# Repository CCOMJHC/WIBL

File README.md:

# Low-cost Data Logger System

## Purpose

This repository contains the hardware designs, firmware source code, and supporting applications and libraries for a low-cost data logger aimed at the NMEA ([National Marine Electronics Association](https://www.nmea.org)) 0183 and 2000 protocols, as used in many marine electronics systems.  The goal is to provide a minimally-functional system to record the data appearing on NMEA0183 and NMEA2000 busses on board ships, which can be used to provide volunteer depth observations (and many other things) to assist in mapping the oceans.

## Why Have Another Logger?

There is a robust infrastructure of data loggers for both NMEA0183 and NMEA2000 busses, but they are often intended for different purposes (e.g., voyage data recorders, WiFi gateways, etc.), and they are typically order US$250 [2020] or more.  This project came out of efforts within the [Seabed 2030](https://seabed2030.gebco.net) project to map the world ocean completely by 2030, where large-scale mapping is required if the goals of the programme are to be met.  Consequently, while volunteer data is a part of the solution, it has to be something that can be scaled to very large data collections.  Since it has proven hard to sustain open data collection of this type (most of the sustained efforts have been closed, with data only going back to the collectors, and not to open databases), we believe that the only viable financial model for this purpose is to give the hardware away for free, rather than attempting to sell it for profit.  That is, the hardware is free to the data collector, who is asked just to host the hardware on their ship.  Because of this model, we need the hardware to be as low-cost as possible.

This project is therefore aimed at designing as simple, and low-cost, a logger as possible, so that as many as possible can be built and distributed to assist in mapping the oceans.  The target price is order US$30 [2020] for one interface (either NMEA0183 or NMEA2000), or US$40 [2020] for both interfaces.

At the same time, we recognise that getting data from the loggers into the national and international databases can be difficult, and ask a lot of the volunteer data collectors.  The project is therefore also attempting to define a workflow for submission of data to the [International Hydrographic Office](https://iho.int)'s [Data Center for Digital Bathymetry](https://www.ngdc.noaa.gov/iho/), hosted by the [National Centers for Environmental Information](https://www.ngdc.noaa.gov) in Boulder, CO.  The goal is to have a "Trusted Node in a Box", so that anyone wanting to support collection of data of this kind has everything they need to support a very basic data flowpath direct from the loggers through the cloud to DCDB.  (Developers are then free to add on anything else they need.)

## What Does the Logger Do?

The logger's functionality is deliberately constrained.  During normal operations, the logger monitors the NMEA0183 and/or NMEA2000 busses to which it is attached, and records any valid data packet received to local storage.  Timestamps are provided through the elapsed time counter on the microcontroller used, and although a pseudo-time is computed from NMEA2000 data packets if they are available, there is no expectation that timestamps will be assigned until the data is uploaded for processing.

The logger provides a WiFi interface for monitoring, configuration, and control.  If there's no other option, the logger will provide its own access point (i.e., create its own WiFi network) to which users can connect, but it can also be configured to connect to a mobile hotspot or an infrastructure WiFi network if available.  The logger runs a web server so that any modern browser can be used to interact with the system (the logger provides the HTML and JavaScript for all required functionality), and also provides an API to send simple commands using a custom language and receive JSON-format responses for a programmatic interface.

After upload to a mobile collection device (e.g., a cell-phone or tablet), or direct uploading (via a separate upload server, also included, if the logger is on an infrastructure network with internet connection), the data is sent to Amazon Web Services, at which point it is processed, reformatted, packaged, and transmitted to DCDB for archive.

## Concept of Operations

This logger is designed for supported, focussed, data collections.  In this mode, loggers would be provided by an organisation in a specific geographic location to support data collection in a particular area.  The goal here is to provide density of observations in an area, which greatly assists in processing the data, and making useful products.  In addition to providing the loggers (and recruiting the volunteer observers), the organisation would also provide local support personnel to visit the volunteer observers, pick up the collected data (via mobile device or through maintaining an upload server), and make sure that the loggers were still collecting data.  Having local support also ensures that there is continued communication with the observers, which is useful in sustaining the community in the long term.

After each visit, all of the data collected (potentially from multiple observers) on the mobile device can be uploaded to any available service that implements the cloud segment of the software suite.  This could be something set up specifically for the organisation using the model provided here, or it could be a third-party that provides an equivalent.

## Licensing and Distribution

In order to provide for the widest possible use (and to avoid excuses ...) the hardware designs, firmware source, and supporting libraries are all released as Open Source under the MIT license.  The cloud segment is released under the MIT License for non-commercial use; for commercial licenses, please contact info@ccom.unh.edu.

## Where to Start

See the "Logger firmware" section below to get started with the WIBL loggers. 
See the "Data management" section below to get started using WIBL and 
`wibl-python` tools to manage and process data generated by WIBL loggers.

### Logger firmware

The source for the system is maintained in a [GitHub repository](https://github.com/CCOMJHC/WIBL), which also includes a [Wiki](https://github.com/CCOMJHC/WIBL/wiki) for details of the design and system development.  The Wiki is the most useful source of current information to set up and programme the logger firmware, and to access the rest of the code resources.

To build the firmware and work with the hardware designs, you will need at least:

1. A functional Python interpreter (at least 3.13) (e.g., [MiniConda](https://www.anaconda.com/docs/getting-started/miniconda/main)).

2. A working copy of [VSCode](https://code.visualstudio.com) and [PlatformIO](https://platformio.org) to build the firmware and other logger functionality.

3. Support for NMEA2000 handling on ESP32 (you need the [base library](https://github.com/ttlappalainen/NMEA2000) and [ESP-specific](https://github.com/ttlappalainen/NMEA2000_esp32) extensions).

4. [KiCAD](https://www.kicad.org) (at least 9.0) to examine and edit the logger schematic and board layout.

5. [FreeCAD](https://www.freecad.org) (at least 1.0) to examine and edit the logger enclosure STEP files.

6. A working C++11 (at least) compiler for the software data simulator (the installation with VSCode works very well).

With these prerequisites, the recommended place to start is with the logger firmware, followed by the post-processing Python code, which will allow you to demonstrate that your logger is actually logging data.  For benchtop testing, the hardware data simulator can be used to generate simulated data on both NMEA0183 and NMEA2000 buses for testing logger modifications.

### Data management

The included [wibl-python](wibl-python/README.md) tools allow data from WIBL 
loggers to be processed into GeoJSON format and to be submitted to 
[DCDB](https://www.ngdc.noaa.gov/iho/). There is also a tool called 
[LogConvert](LogConvert) that allows data from TeamSurv and Yacht Devices
loggers to be converted to WIBL format for further processing using 
`wibl-python`.

An easy way to use both `wibl-python` and `LogConvert` is to use the official
WIBL [container images](DataManagement/containers/README.md).

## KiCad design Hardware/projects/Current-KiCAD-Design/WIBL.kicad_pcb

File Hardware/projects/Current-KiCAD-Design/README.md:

# KiCAD Hardware Design Files

## Introduction

This directory contains all of the files required for the [KiCAD](https://www.kicad.org) projects associated with the [WIBL](https://wibl.ccom.unh.edu) project.  You will need at least v. 10.0 of KiCAD to use the files.

## Portability

There have been some reported issues with project files containing hard-coded directory and filenames, which makes them a little less portable than would be preferred.  If this happens, you can point at the new location of schematic symbols and footprint libraries by:

1. Open [the project file](WIBL.kicad_pro) in KiCAD.
2. Open menu Peferences > Manage Symbol Libraries
    - Switch to the "Project Specific Libraries" tab.
    - Click on the cell containing the pathname for the "WIBL-sym" library, and navigate to the [WIBL.kicad_sym](WIBL.kicad_sym) file.
    - Click "OK" to save.
3. Open menu Preferences > Manage Footprint Libraries
    - Switch to the "Project Specific Libraries" tab.
    - Click on the cell containing the pathname for the "WIBL" library, and navigate to the [WIBL.pretty](WIBL.pretty/) directory.
    - Click "OK" to save.

After this, you can check that the project is working appropriately by using the Electrical Rules Check (ERC) in schematic editor, and Design Rules Check (DRC) in PCB editor.  There may be one or two warnings, but there shouldn't be a tonne of warnings about missing libraries or symbols.

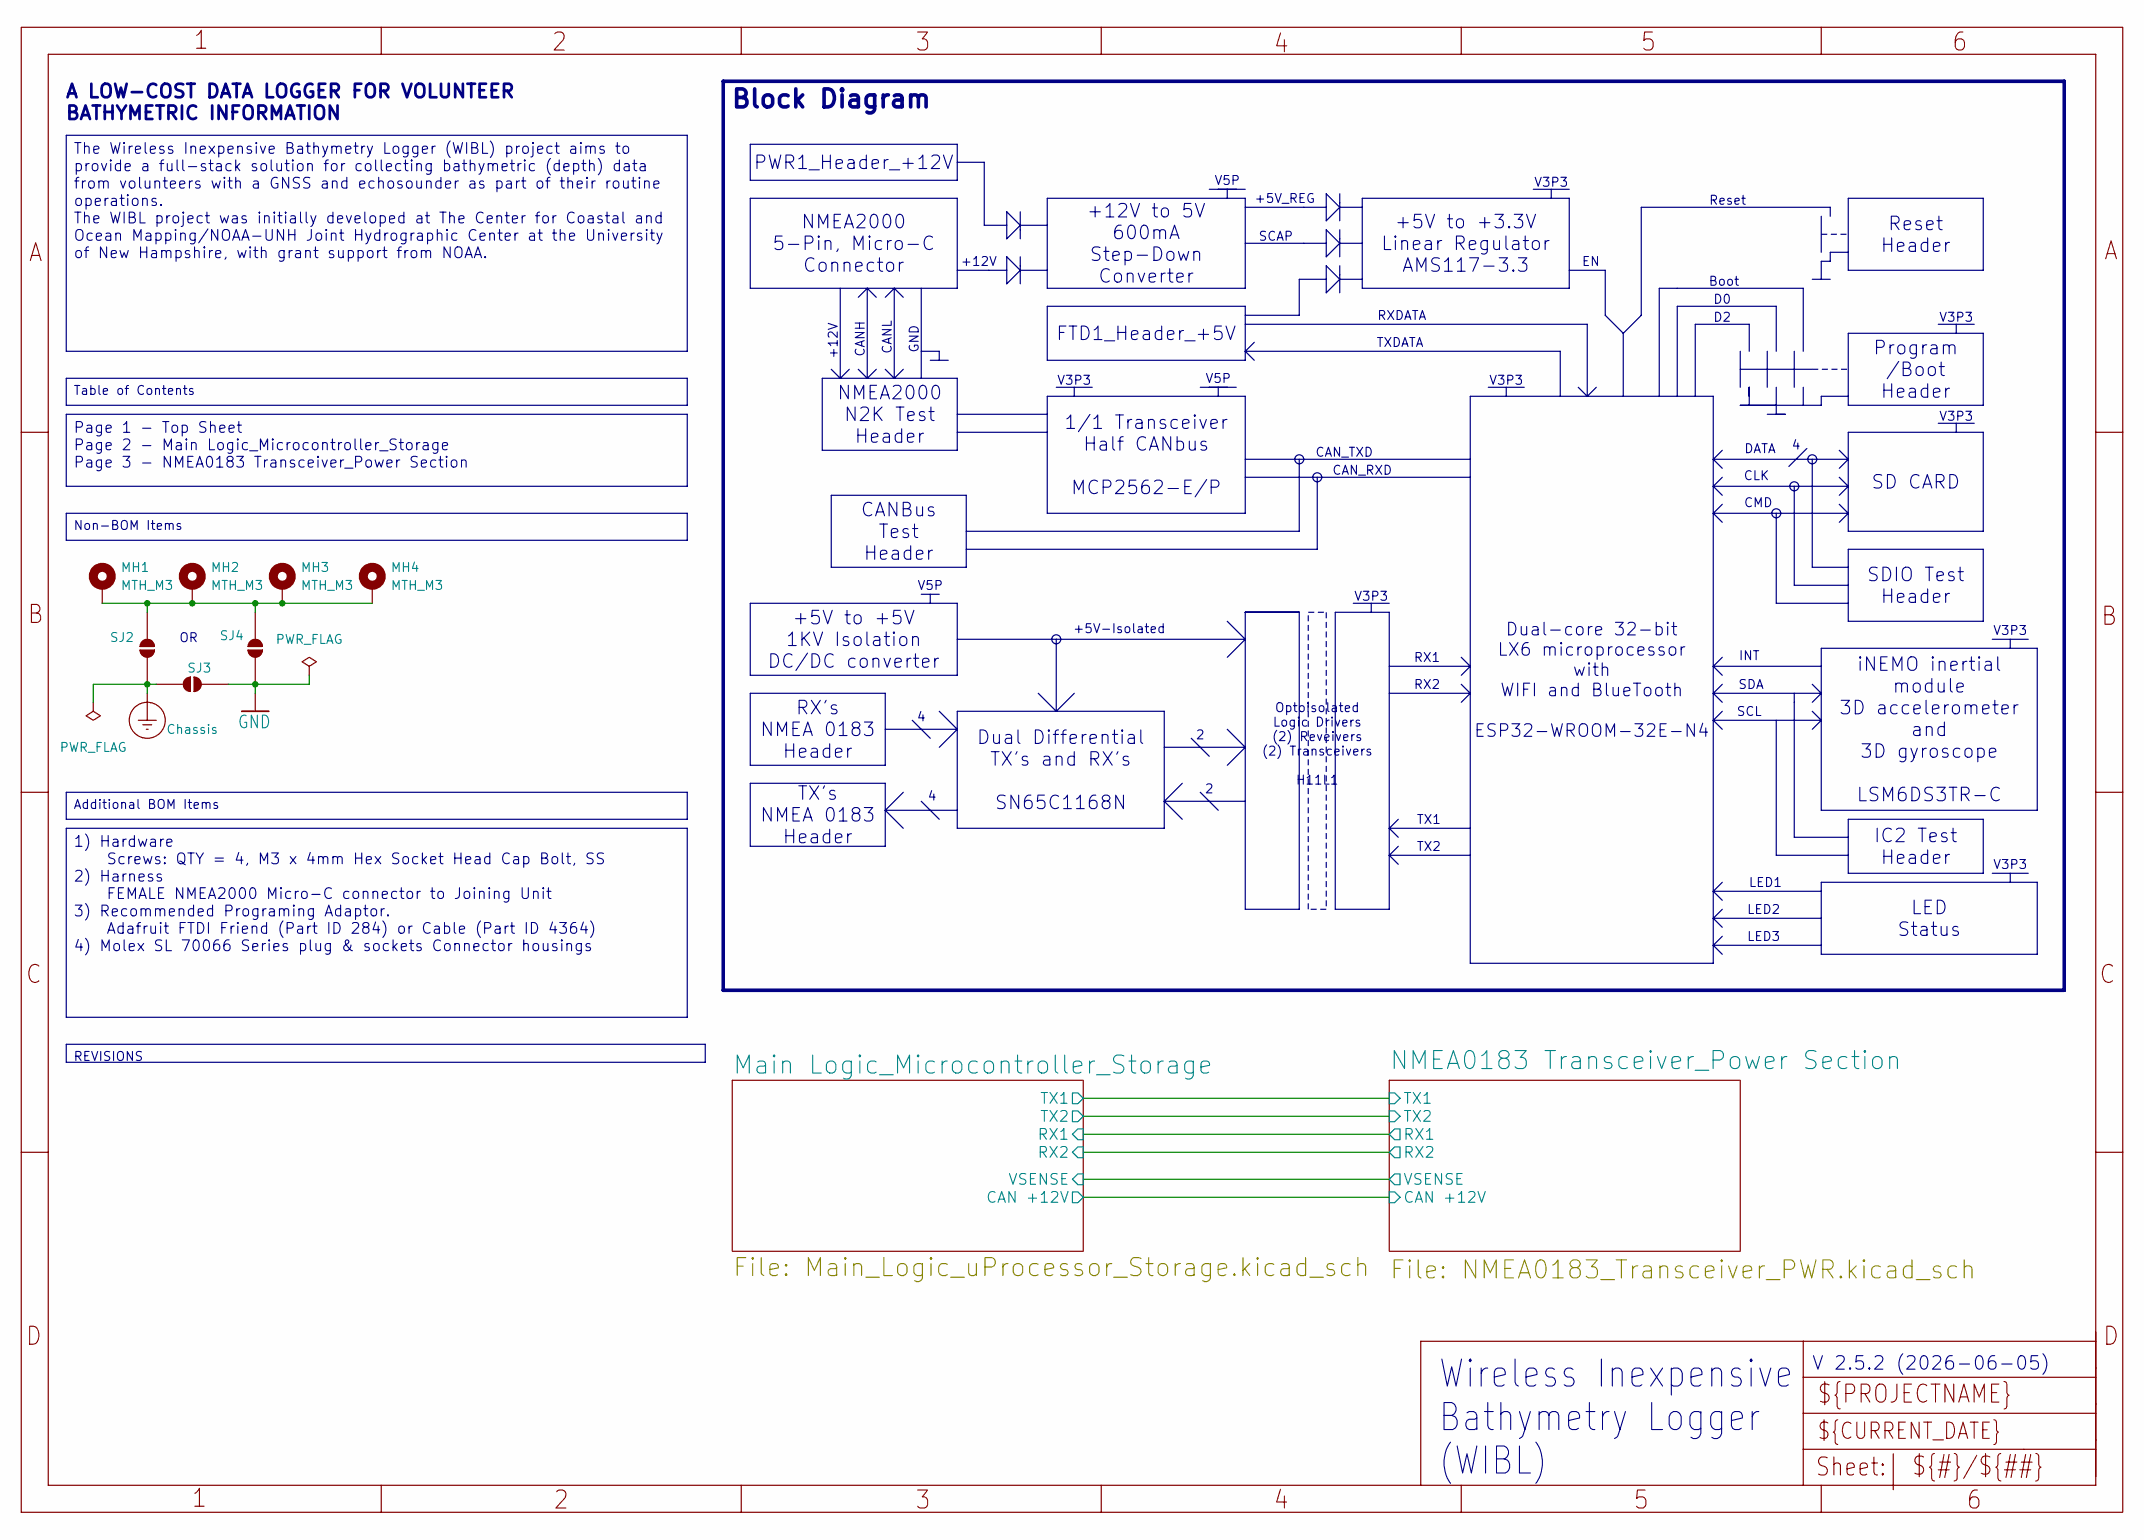
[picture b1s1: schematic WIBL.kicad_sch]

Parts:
MH1, MH2, MH3, MH4: MTH_M3; MountingHole_3.2mm_M3_DIN965_Pad_TopBottom
SJ2, SJ3, SJ4: SJ_NO; SolderJumper-2_P1.3mm_Open_RoundedPad1.0x1.5mm

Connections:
Chassis: SJ2.1 (A), SJ3.2 (B); also elsewhere on the board
GND: SJ3.1 (A), SJ4.1 (A); also elsewhere on the board
unnamed: MH1.1 (1_1), MH2.1 (1_1), MH3.1 (1_1), MH4.1 (1_1), SJ2.2 (B), SJ4.2 (B)

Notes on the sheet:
+5V_REG
V5P
V3P3
RX1
V 2.5.2 (2026-06-05)
TX1
CMD
+5V-Isolated
LED3
CANL
RX2
DATA
CAN_RXD
SCL
Reset
Boot
CANH
GND
SDA
TXDATA
A LOW-COST DATA LOGGER FOR VOLUNTEER BATHYMETRIC INFORMATION
+12V
RXDATA
Wireless Inexpensive Bathymetry Logger (WIBL)
TX2
Optoisolated Logic Drivers (2) Reveivers (2) Transceivers H11L1
LED1
LED2
CAN_TXD
SCAP
CLK
INT
TX's NMEA 0183 Header
REVISIONS
1) Hardware Screws: QTY = 4, M3 x 4mm Hex Socket Head Cap Bolt, SS 2) Harness FEMALE NMEA2000 Micro-C connector to Joining Unit 3) Recommended Programing Adaptor. Adafruit FTDI Friend (Part ID 284) or Cable (Part ID 4364) 4) Molex SL 70066 Series plug & sockets Connector housings
SDIO Test Header
Page 1 - Top Sheet Page 2 - Main Logic_Microcontroller_Storage Page 3 - NMEA0183 Transceiver_Power Section
FTD1_Header_+5V
Dual Differential TX's and RX's SN65C1168N
+12V to 5V 600mA Step-Down Converter

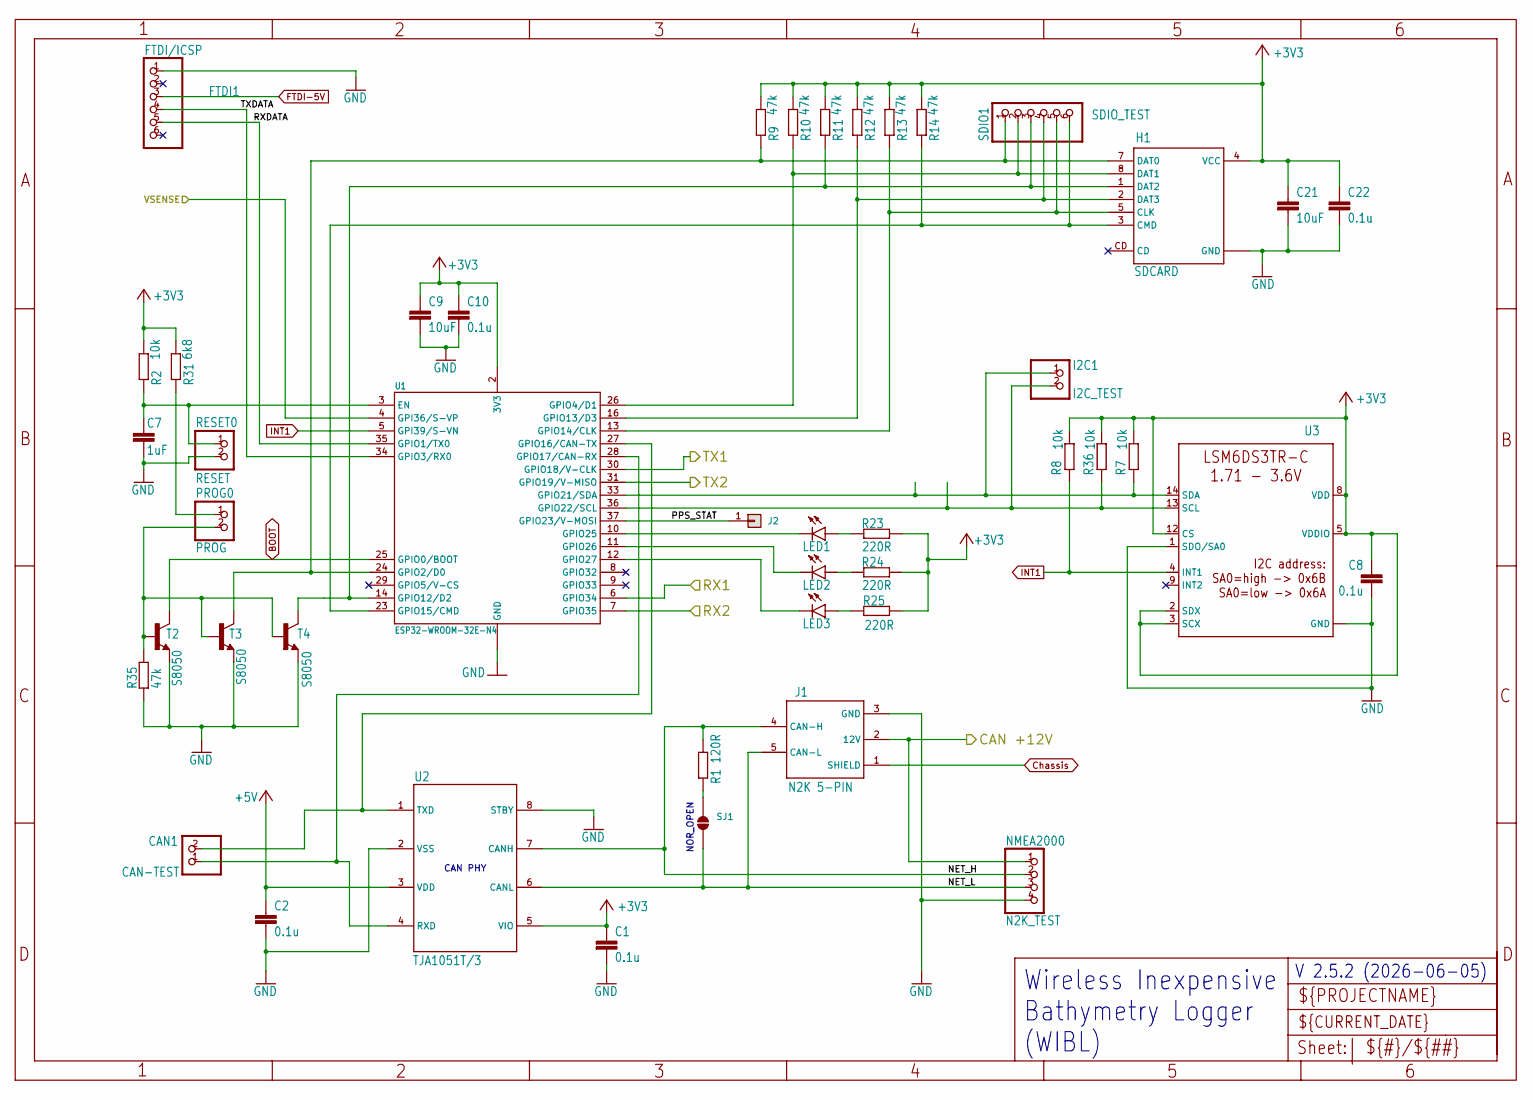
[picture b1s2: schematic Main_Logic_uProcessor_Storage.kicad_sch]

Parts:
C1, C2, C8, C10, C22: 0.1u; C0805_334
C7: 1uF; C0805_334
C9, C21: 10uF; C0805_334
CAN1: CAN-TEST; 1X02_325_254mm; MPNum PZ254V-11-02P
FTDI1: FTDI/ICSP; 1X06_325_254mm; MPNum PZ254V-11-06P
H1: SDCARD; XUNPU-MICROSD-SOCKET; MPNum TF-115
I2C1: I2C_TEST; 1X02_325_254mm; MPNum PZ254V-11-02P
J1: N2K 5-PIN; NMEA2000; MPNum HMC-05PMMS-SF8001
J2: Conn_01x01; PinHeader_1x01_P2.54mm_Vertical
LED1: LEDCHIP-LED0603; CHIP-LED0603_259; MPNum 19-213/Y2C-CQ2R2L/3T(CY)
LED2: LEDCHIP-LED0603; CHIP-LED0603_259; MPNum 19-217/GHC-YR1S2/3T
LED3: LEDCHIP-LED0603; CHIP-LED0603_259; MPNum 19-217/BHC-ZL1M2RY/3T
NMEA2000: N2K_TEST; 1X04_325_254mm; MPNum PZ254V-11-04P
PROG0: PROG; 1X02_325_254mm; MPNum PZ254V-11-02P
R1: 120R; R0805_334
R2, R7, R8, R36: 10k; R0805_334
R9, R10, R11, R12, R13, R14, R35: 47k; R0805_334
R23, R24, R25: 220R; R0805_334
R31: 6k8; R0805_334
RESET0: RESET; 1X02_325_254mm; MPNum PZ254V-11-02P
SDIO1: SDIO_TEST; 1X06_325_254mm; MPNum PZ254V-11-06P
SJ1: SJ_NO; SolderJumper-2_P1.3mm_Open_RoundedPad1.0x1.5mm
T2, T3, T4: S8050; SOT23_402; MPNum S8050
U1: ESP32-WROOM-32E-N4; ESPS32-WROOM-32E; MPNum ESP32-WROOM-32E-N4
U2: TJA1051T/3; SOIC8; MPNum MCP2562T-E/SN
U3: LSM6DS3TR-C; LGA-14-2.5X3MM; MPNum LSM6DS3TR-C

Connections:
+3V3: C1.1, C8.1, C9.1, C10.1, C21.1, C22.1, H1.4 (VCC), R2.2, R7.2, R8.2, R9.2, R10.2, R11.2, R12.2, R13.2, R14.2, R23.1, R24.1, R25.1, R31.2, R36.2, U1.2 (3V3), U2.5 (VIO), U3.2 (SDX), U3.3 (SCX), U3.5 (VDDIO), U3.8 (VDD), U3.12 (CS); also elsewhere on the board
+5V: C2.1, U2.3 (VDD); also elsewhere on the board
/Main Logic_Microcontroller_Storage/CAN +12V: J1.2 (12V), NMEA2000.1; also elsewhere on the board
/Main Logic_Microcontroller_Storage/NET_H: J1.4 (CAN-H), NMEA2000.2, R1.2, U2.7 (CANH)
/Main Logic_Microcontroller_Storage/NET_L: J1.5 (CAN-L), NMEA2000.3, SJ1.1 (A), U2.6 (CANL)
/Main Logic_Microcontroller_Storage/PPS_STAT: J2.1 (Pin_1_1), U1.37 (GPIO23/V-MOSI)
/Main Logic_Microcontroller_Storage/RX1: U1.6 (GPIO34); also elsewhere on the board
/Main Logic_Microcontroller_Storage/RX2: U1.7 (GPIO35); also elsewhere on the board
/Main Logic_Microcontroller_Storage/RXDATA: FTDI1.5, U1.35 (GPIO1/TX0)
/Main Logic_Microcontroller_Storage/TX1: U1.30 (GPIO18/V-CLK); also elsewhere on the board
/Main Logic_Microcontroller_Storage/TX2: U1.31 (GPIO19/V-MISO); also elsewhere on the board
/Main Logic_Microcontroller_Storage/TXDATA: FTDI1.4, U1.34 (GPIO3/RX0)
/NMEA0183 Transceiver_Power Section/VSENSE: U1.4 (GPI36/S-VP); also elsewhere on the board
BOOT: T2.3 (C), U1.25 (GPIO0/BOOT); also elsewhere on the board
Chassis: J1.1 (SHIELD); also elsewhere on the board
FTDI-5V: FTDI1.3; also elsewhere on the board
GND: C1.2, C2.2, C7.2, C8.2, C9.2, C10.2, C21.2, C22.2, FTDI1.1, H1.6 (GND), H1.GND1 (GND), H1.GND2 (GND), H1.GND3 (GND), H1.GND4 (GND), J1.3 (GND), NMEA2000.4, R35.1, RESET0.2, T2.2 (E), T3.2 (E), T4.2 (E), U1.1 (GND), U1.15 (GND), U1.38 (GND), U1.THERM (GND), U2.2 (VSS), U2.8 (STBY), U3.1 (SDO/SA0), U3.6 (GND), U3.7 (GND); also elsewhere on the board
INT1: R8.1, U1.5 (GPI39/S-VN), U3.4 (INT1)
unnamed: H1.5 (CLK), R13.1, SDIO1.5, U1.13 (GPIO14/CLK)
unnamed: H1.3 (CMD), R14.1, SDIO1.6, U1.23 (GPIO15/CMD)
unnamed: H1.7 (DAT0), R9.1, SDIO1.1, T3.3 (C), U1.24 (GPIO2/D0)
unnamed: H1.8 (DAT1), R10.1, SDIO1.2, U1.26 (GPIO4/D1)
unnamed: H1.1 (DAT2), R11.1, SDIO1.3, T4.3 (C), U1.14 (GPIO12/D2)
unnamed: H1.2 (DAT3), R12.1, SDIO1.4, U1.16 (GPIO13/D3)
unnamed: LED1.A, R23.2
unnamed: LED2.A, R24.2
unnamed: LED3.A, R25.2
unnamed: PROG0.1, R31.1
unnamed: R1.1, SJ1.2 (B)
unnamed: PROG0.2, R35.2, T2.1 (B), T3.1 (B), T4.1 (B)
unnamed: C7.1, R2.1, RESET0.1, U1.3 (EN)
unnamed: CAN1.2, U1.27 (GPIO16/CAN-TX), U2.1 (TXD)
unnamed: CAN1.1, U1.28 (GPIO17/CAN-RX), U2.4 (RXD)
unnamed: I2C1.1, R7.1, U1.33 (GPIO21/SDA), U3.14 (SDA)
unnamed: I2C1.2, R36.1, U1.36 (GPIO22/SCL), U3.13 (SCL)
unnamed: LED1.C, U1.10 (GPIO25)
unnamed: LED2.C, U1.11 (GPIO26)
unnamed: LED3.C, U1.12 (GPIO27)

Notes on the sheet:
Wireless Inexpensive Bathymetry Logger (WIBL)
V 2.5.2 (2026-06-05)
CAN PHY
NOR_OPEN

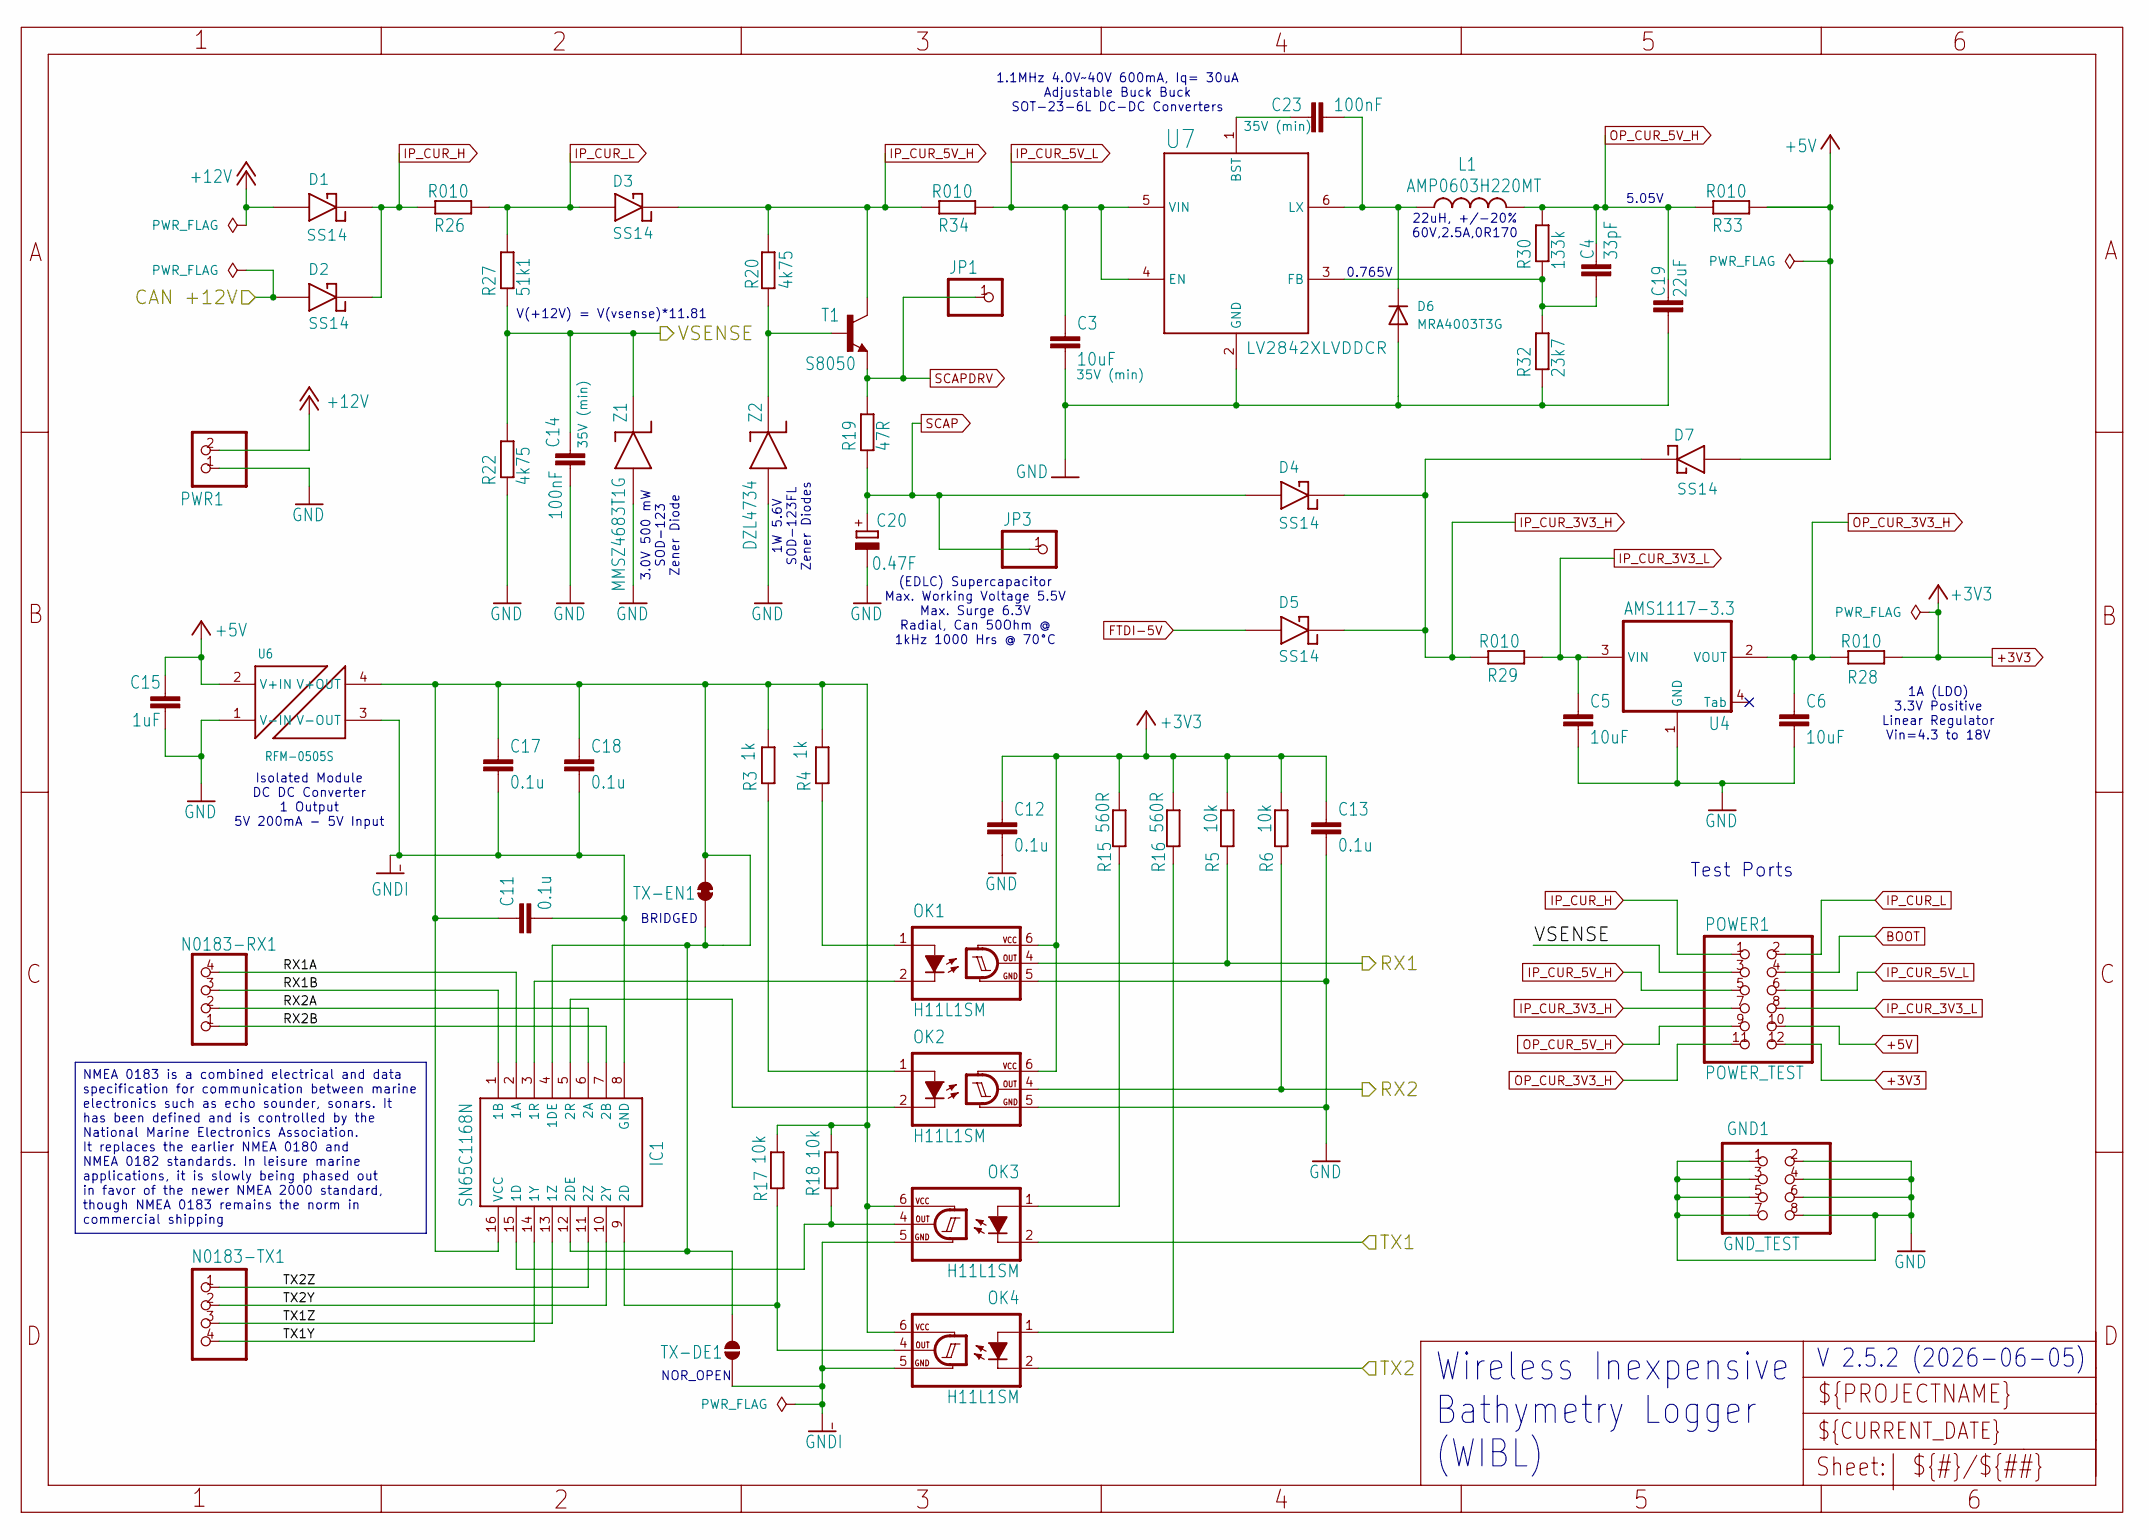
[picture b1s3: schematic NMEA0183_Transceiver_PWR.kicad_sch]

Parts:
C3: 10uF; C1206_334; Voltage 35V (min)
C4: 33pF; C0603_334
C5, C6: 10uF; C0805_334
C11, C12, C13, C17, C18: 0.1u; C0805_334
C14: 100nF; C0402; Voltage 35V (min)
C15: 1uF; C0805_334
C19: 22uF; C0603_334
C20: 0.47F; P128-50_334; Working Voltage 5.5V; MPNum KR-5R5C474-R
C23: 100nF; C0402
D1, D2, D3, D4, D5, D7: SS14; DO-214AC; MPNum SS14
D6: MRA4003T3G; DO-214AC_p12
GND1: GND_TEST; 2X04_325; MPNum PZ254V-12-4P
IC1: SN65C1168N; DIP794W53P254L1930H508Q16N; MPNum SN65C1168N
JP1, JP3: PINHD-1X1; 1X01_325_254mm; MPNum PZ254V-11-01P
L1: AMP0603H220MT; MWSA0603S; MPNum AMP0603H220MT, MWSA0603S-220MT
N0183-RX1: PINHD-1X4; 1X04_325_254mm; MPNum PZ254V-11-04P
N0183-TX1: TX_TEST; 1X04_325_254mm; MPNum PZ254V-11-04P
OK1, OK2, OK3, OK4: H11L1SM; DIL6-SMD_320; MPNum H11L1SM
POWER1: POWER_TEST; 2X06_325; MPNum PZ254V-12-6P
PWR1: PINHD-1X2; 1X02_325_254mm; MPNum PZ254V-11-02P
R3, R4: 1k; R0805_334
R5, R6, R17, R18: 10k; R0805_334
R15, R16: 560R; R0805_334
R19: 47R; R0805_334
R20: 4k75; R0805_334
R22: 4k75; R0603_334
R26, R28, R29, R33, R34: R010; R0603_334
R27: 51k1; R0603_334
R30: 133k; R0603_334
R32: 23k7; R0603_334
T1: S8050; SOT23_402; MPNum S8050
TX-DE1: SJ_NO; SolderJumper-2_P1.3mm_Open_RoundedPad1.0x1.5mm
TX-EN1: SJ_NC; SolderJumper-2_P1.3mm_Bridged2Bar_Pad1.0x1.5mm
U4: AMS1117-3.3; SOT223_111; Voltage (V) 3.3; MPNum UMW AMS1117-3.3
U6: RFM-0505S; MPNum RFM-0505S
U7: LV2842XLVDDCR; SOT-23-6L; MPNum LV2842XLVDDCR
Z1: MMSZ4683T1G; SOD123; Voltage 3V; MPNum BZT52C3V0-7-F
Z2: DZL4734; SOD-123FL; MPNum DZL4734

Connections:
+3V3: C12.1, C13.1, OK1.6 (VCC), OK2.6 (VCC), POWER1.12, R5.2, R6.2, R15.2, R16.2, R28.1; also elsewhere on the board
+5V: C15.1, D7.A, POWER1.10, R33.1, U6.2 (V+IN); also elsewhere on the board
+12V: D1.A, PWR1.2
/Main Logic_Microcontroller_Storage/CAN +12V: D2.A; also elsewhere on the board
/Main Logic_Microcontroller_Storage/RX1: OK1.4 (OUT), R5.1; also elsewhere on the board
/Main Logic_Microcontroller_Storage/RX2: OK2.4 (OUT), R6.1; also elsewhere on the board
/Main Logic_Microcontroller_Storage/TX1: OK3.2 (C); also elsewhere on the board
/Main Logic_Microcontroller_Storage/TX2: OK4.2 (C); also elsewhere on the board
/NMEA0183 Transceiver_Power Section/RX1A: IC1.2 (1A), N0183-RX1.4
/NMEA0183 Transceiver_Power Section/RX1B: IC1.1 (1B), N0183-RX1.3
/NMEA0183 Transceiver_Power Section/RX2A: IC1.6 (2A), N0183-RX1.2
/NMEA0183 Transceiver_Power Section/RX2B: IC1.7 (2B), N0183-RX1.1
/NMEA0183 Transceiver_Power Section/TX1Y: IC1.14 (1Y), N0183-TX1.4
/NMEA0183 Transceiver_Power Section/TX1Z: IC1.13 (1Z), N0183-TX1.3
/NMEA0183 Transceiver_Power Section/TX2Y: IC1.10 (2Y), N0183-TX1.2
/NMEA0183 Transceiver_Power Section/TX2Z: IC1.11 (2Z), N0183-TX1.1
/NMEA0183 Transceiver_Power Section/VSENSE: C14.P$1 (1), POWER1.3, R22.2, R27.1, Z1.2 (K); also elsewhere on the board
BOOT: POWER1.4; also elsewhere on the board
FTDI-5V: D5.A; also elsewhere on the board
GND: C3.2, C5.2, C6.2, C12.2, C13.2, C14.P$2 (2), C15.2, C19.1, C20.-, D6.2 (A), GND1.1, GND1.2, GND1.3, GND1.4, GND1.5, GND1.6, GND1.7, GND1.8, OK1.5 (GND), OK2.5 (GND), PWR1.1, R22.1, R32.1, U4.1 (GND), U6.1 (V-IN), U7.2 (GND), Z1.1 (A), Z2.A; also elsewhere on the board
GNDI: C11.2, C17.2, C18.2, IC1.8 (GND), OK3.5 (GND), OK4.5 (GND), TX-DE1.1 (A), U6.3 (V-OUT)
IP_CUR_3V3_H: D4.K, D5.K, D7.K, POWER1.7, R29.2
IP_CUR_3V3_L: C5.1, POWER1.8, R29.1, U4.3 (VIN)
IP_CUR_5V_H: D3.K, POWER1.5, R20.2, R34.2, T1.3 (C)
IP_CUR_5V_L: C3.1, POWER1.6, R34.1, U7.4 (EN), U7.5 (VIN)
IP_CUR_H: D1.K, D2.K, POWER1.1, R26.2
IP_CUR_L: D3.A, POWER1.2, R26.1, R27.2
unnamed: C23.P$1 (1), U7.1 (BST)
unnamed: C23.P$2 (2), D6.1 (K), L1.P$1 (1), U7.6 (LX)
unnamed: IC1.15 (1D), OK3.4 (OUT), R18.1
unnamed: C11.1, C17.1, C18.1, IC1.4 (1DE), IC1.12 (2DE), IC1.16 (VCC), OK3.6 (VCC), OK4.6 (VCC), R3.2, R4.2, R17.2, R18.2, TX-DE1.2 (B), TX-EN1.1 (A), TX-EN1.2 (B), U6.4 (V+OUT)
unnamed: IC1.3 (1R), OK1.2 (C)
unnamed: IC1.9 (2D), OK4.4 (OUT), R17.1
unnamed: IC1.5 (2R), OK2.2 (C)
unnamed: OK1.1 (A), R4.1
unnamed: OK2.1 (A), R3.1
unnamed: OK3.1 (A), R15.1
unnamed: OK4.1 (A), R16.1
unnamed: R20.1, T1.1 (B), Z2.K
unnamed: C4.1, R30.1, R32.2, U7.3 (FB)
OP_CUR_3V3_H: C6.1, POWER1.11, R28.2, U4.2 (VOUT)
OP_CUR_5V_H: C4.2, C19.2, L1.P$2 (2), POWER1.9, R30.2, R33.2
SCAP: C20.+, D4.A, JP3.1 (1_1), R19.1
SCAPDRV: JP1.1 (1_1), R19.2, T1.2 (E)

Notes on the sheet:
0.765V
5.05V
1A (LDO) 3.3V Positive Linear Regulator Vin=4.3 to 18V
1W 5.6V SOD-123FL Zener Diodes
3.0V 500 mW SOD-123 Zener Diode
V(+12V) = V(vsense)*11.81
Test Ports
Isolated Module DC DC Converter 1 Output 5V 200mA - 5V Input
1.1MHz 4.0V~40V 600mA, Iq= 30uA Adjustable Buck Buck SOT-23-6L DC-DC Converters
22uH, +/-20% 60V,2.5A,0R170
V 2.5.2 (2026-06-05)
NOR_OPEN
BRIDGED
(EDLC) Supercapacitor Max. Working Voltage 5.5V Max. Surge 6.3V Radial, Can 50Ohm @ 1kHz 1000 Hrs @ 70°C
Wireless Inexpensive Bathymetry Logger (WIBL)
NMEA 0183 is a combined electrical and data specification for communication between marine electronics such as echo sounder, sonars. It has been defined and is controlled by the National Marine Electronics Association. It replaces the earlier NMEA 0180 and NMEA 0182 standards. In leisure marine app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

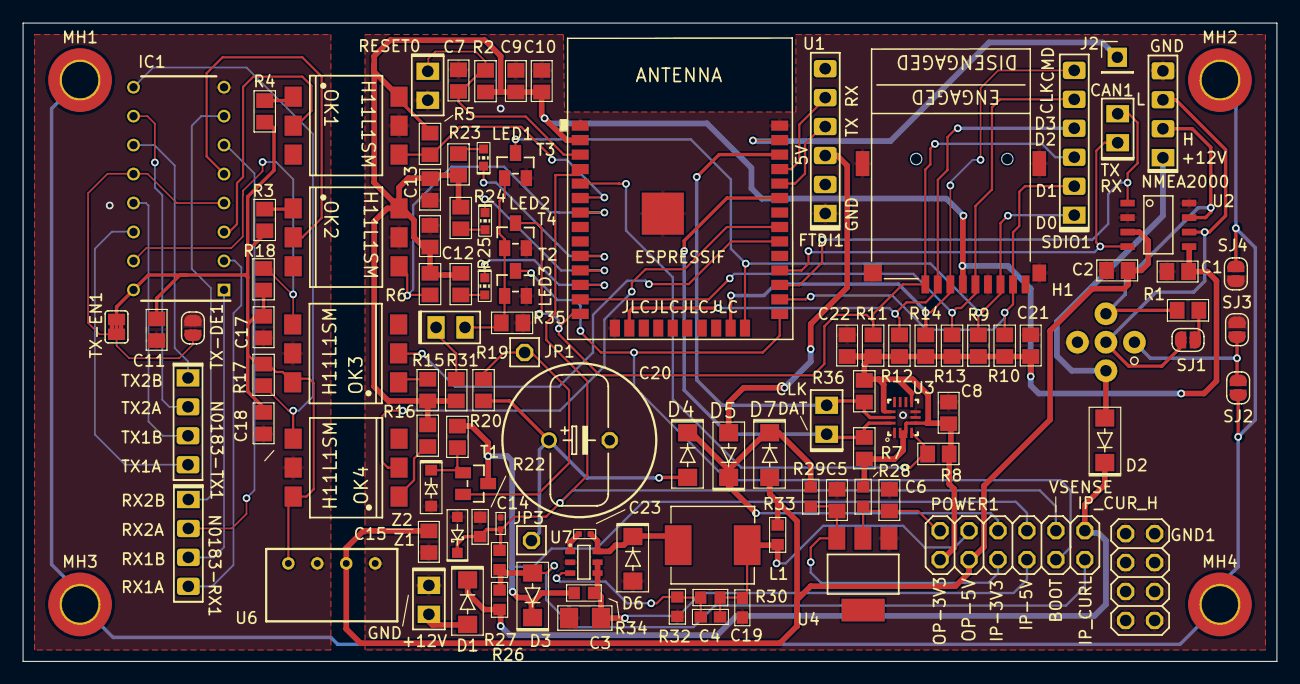
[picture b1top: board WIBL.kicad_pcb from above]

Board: 2 copper layers, 110.0 x 56.0 mm, 113 parts (1 on the bottom side), 72 nets.

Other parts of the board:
G1: LOGO; CCOM_JHC_Logo_rt_18mm

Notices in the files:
Hardware/projects/Current-KiCAD-Design/WIBL.kicad_pcb:
(c) 2025 Center for Coastal and Ocean Mapping
Hardware/projects/TCB-GNSS-Board/WIBL-TCB.kicad_pcb:
https://creativecommons.org/licenses/by-sa/4.0
Released under the Creative Commons Attribution Share-Alike 4.0 License
